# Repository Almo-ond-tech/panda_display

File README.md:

# panda_display

# Description

A spotify display in the form of a red pandas. You can see which song you're listening to, the album cover and the name of the artist on the display. Switch 1 goes to the previous song, switch 2 pauses the track and switch 3 skips the track you're currently listening to.
  
# Reason
I made this project as a gift for my friend who loves listening to music on spotify. I thought it would look nice as a decoration in their room and because they love red panda. The case is a bit too big, but I think it's fine since it also serves as an aesthetic features. They also like 3d modeling stuff so that's why I intentionally didn't model the keycaaps so they could customise it themselves.

# Firmware Setup
I used a spotify library that's a wrapper for the Spotify Web API designed to work with the ESP32 microcontroller from 
<a href= 'https://github.com/FinianLandes/SpotifyEsp32#setup'> FinianLandes/SpotifyEsp32. </a> It also contains a more in depth tutorial on how to set it up.
To start you should have a <b>spotify developer's account</b> and replace the <b>Client Id</b> and <b>Client Secret</b> with your own in the sketch. Then fill this in the redirect uri:

Enable the <b> Web API </b> option.

Also replace the ssid and password to match the wifi you're going to be using. If you don't know the ssid of your wifi network it will be printed in the serial monitor while the esp tries to connect to a nearby network. Then you can set the ssid and it will be connected to the internet.
After logging in via the URL shown in the Serial Monitor, your ESP32 will print a refresh token.
Copy this token and pass it as the third parameter to the constructor.
Spotify sp(CLIENT_ID, CLIENT_SECRET, REFRESH_TOKEN);

## Disclaimer
What I have now is currently untested so the firmware and the casing will definitely need some adjusting depending on how everything turns out

<h3><b>The blue crossed out pins on the display match the header pins in that exact order. Starting from pin 2 to pin 12</b></h3>

# Building the Case

<a href='https://cad.onshape.com/documents/bfc07541df551773d29ac83e/w/7fb00ae2864c3e517c62e19a/e/fd3725dd2f3859ce92e0f7f4'> Onshape Link </a> Or else copy paste in your browser : [https://cad.onshape.com/documents/bfc07541df551773d29ac83e/w/7fb00ae2864c3e517c62e19a/e/fd3725dd2f3859ce92e0f7f4]

<h4>Step 1:</h4> Glue all the componets for the Face and Tail indivudually after printing everything in your preferred colors with a strong adhesive. 
For the Body glue all the parts together <b>excluding the bottom case</b>.  <br>
 For the Face make sure to glue with the parts facing the right direction.  <br>
 For the Tail make sure to glue the parts in the right order.

<h4>Step 2:</h4> Attach the full case together <b>Still excluding the bottom case</b>.

<h4>Step 3:</h4> Fasten all the electrical pieces inside the Body. 

<h4>Step 4:</h4> 
Secure the bottom case in place and your Red Panda Display is now complete!

## BOM (Bill of Materials)
[tablemagic_with_total.csv](https://github.com/user-attachments/files/29109595/tablemagic_with_total.csv)

| Item                                                                                            | Description                               | Quantity | Unit Price ($) | Total Price | URL                                                                                                                                                                                                                                                                                                                                                                                                                                                                                                                                                                                                                                                                                                                                                                                                                                                                                                                                        | Running Total ($ with Tax) |
|-------------------------------------------------------------------------------------------------|-------------------------------------------|----------|----------------|-------------|--------------------------------------------------------------------------------------------------------------------------------------------------------------------------------------------------------------------------------------------------------------------------------------------------------------------------------------------------------------------------------------------------------------------------------------------------------------------------------------------------------------------------------------------------------------------------------------------------------------------------------------------------------------------------------------------------------------------------------------------------------------------------------------------------------------------------------------------------------------------------------------------------------------------------------------------|----------------------------|
| 1,8  ST7735S TFT LCD-scherm                                                                     | 128x160 ST7735S TFT LCD-screen            | 1        | 3.52           | 3.52        | https://nl.aliexpress.com/item/1005009694512284.html?spm=a2g0o.cart.0.0.53c261d7OkfEao&mp=1&pdp_npi=6%40dis%21EUR%21EUR+6.07%21EUR+3.04%21%21EUR+3.04%21%21%21%402161390417815650514934912e10d2%2112000049877275098%21ct%21NL%213328622363%21%211%210%21&gatewayAdapt=glo2nld                                                                                                                                                                                                                                                                                                                                                                                                                                                                                                                                                                                                                                                              | 3.52                       |
| 40pcs Dupont Wire Kabel 20 cm Female to Female                                                  | 20cm Dupont Wires (12pcs)                 | 1        | 0.0445         | 1.78        | https://nl.aliexpress.com/item/1005009071621102.html?spm=a2g0o.cart.0.0.53c261d7OkfEao&mp=1&pdp_npi=6%40dis%21EUR%21EUR+1.54%21EUR+1.54%21%21EUR+1.54%21%21%21%402161390417815650514934912e10d2%2112000047812726057%21ct%21NL%213328622363%21%211%210%21&gatewayAdapt=glo2nld                                                                                                                                                                                                                                                                                                                                                                                                                                                                                                                                                                                                                                                              | 1.78                       |
| 10 Pieces 2.54mm Single Row Pin Header Connector Strip 12Pin                                    | 12pin Pin Headers (1pc)                   | 1        | 0.207          | 2.07        | https://nl.aliexpress.com/item/4000988113226.html?spm=a2g0o.cart.0.0.53c261d7OkfEao&mp=1&pdp_npi=6%40dis%21EUR%21EUR+1.79%21EUR+1.79%21%21EUR+1.79%21%21%21%402161390417815650514934912e10d2%2110000013202368857%21ct%21NL%213328622363%21%211%210%21&gatewayAdapt=glo2nld                                                                                                                                                                                                                                                                                                                                                                                                                                                                                                                                                                                                                                                                 | 2.07                       |
| C3 PICO V1.0.0 - LOLIN WIFI Bluetooth IOT-bord ESP32-C3FH4                                      | MCU                                       | 1        | 7.77           | 7.77        | https://nl.aliexpress.com/item/1005004866531117.html?spm=a2g0o.cart.0.0.53c261d7OkfEao&mp=1&pdp_npi=6%40dis%21EUR%21EUR+6.69%21EUR+6.69%21%21EUR+6.69%21%21%21%402161390417815650514934912e10d2%2112000056168901173%21ct%21NL%213328622363%21%211%210%21&gatewayAdapt=glo2nld                                                                                                                                                                                                                                                                                                                                                                                                                                                                                                                                                                                                                                                              | 7.77                       |
| 20 Pieces Mechanical Keyboard Switches Red Hot-swappable 3-pin cross stem                       | Keyboard switches (3pcs)                  | 1        | 0.168          | 3.36        | https://nl.aliexpress.com/item/1005011838889689.html?spm=a2g0o.cart.0.0.53c261d7OkfEao&mp=1&pdp_npi=6%40dis%21EUR%21EUR+2.90%21EUR+2.90%21%21EUR+2.90%21%21%21%402161390417815650514934912e10d2%2112000056744509268%21ct%21NL%213328622363%21%211%210%21&gatewayAdapt=glo2nld                                                                                                                                                                                                                                                                                                                                                                                                                                                                                                                                                                                                                                                              | 3.36                       |
| Lithium Polymer Battery 3.7 V 500 mAh 403048 Lipo Rechargeable Battery with Wired JST Connector | Lipo Battery                              | 1        | 11.6           | 11.6        | https://www.amazon.nl/gp/product/B095W6742D/ref=ox_sc_act_title_1?smid=ASLRAS85RTYN3&th=1                                                                                                                                                                                                                                                                                                                                                                                                                                                                                                                                                                                                                                                                                                                                                                                                                                                  | 11.6                       |
| M2.5 screws (50 pcs)                                                                            | 2.5mm diameter pan head screws 6mm (2pcs) | 1        | 0.05           | 2.5         | https://nl.aliexpress.com/item/1005008709978631.html?spm=a2g0o.detail.pcDetailTopMoreOtherSeller.2.454fftMBftMBpy&gps-id=pcDetailTopMoreOtherSeller&scm=1007.40050.354490.0&scm_id=1007.40050.354490.0&scm-url=1007.40050.354490.0&pvid=83f03170-c03f-4f9e-a1b3-7860960ec42c&_t=gps-id%3ApcDetailTopMoreOtherSeller%2Cscm-url%3A1007.40050.354490.0%2Cpvid%3A83f03170-c03f-4f9e-a1b3-7860960ec42c%2Ctpp_buckets%3A668%232846%238114%231999&pdp_ext_f=%7B%22order%22%3A%2211679%22%2C%22eval%22%3A%221%22%2C%22sceneId%22%3A%2230050%22%2C%22fromPage%22%3A%22recommend%22%7D&pdp_npi=6%40dis%21EUR%211.96%211.80%21%21%2114.93%2113.73%21%400b884b5817817984658936804e0fbf%2112000046342342830%21rec%21NL%213328622363%21XZ%211%210%21n_tag%3A-29919%3Bd%3A9b918edc%3Bm03_new_user%3A-29895%3BpisId%3A5000000209393528&utparam-url=scene%3ApcDetailTopMoreOtherSeller%7Cquery_from%3A%7Cx_object_id%3A1005008709978631%7C_p_origin_prod%3A | 2.5                        |
| M3 screws (50 pcs)                                                                              | 3mm diameter pan head screws 6mm (4pcs)   | 1        | 0.0504         | 2.52        | https://nl.aliexpress.com/item/1005008709978631.html?spm=a2g0o.detail.pcDetailTopMoreOtherSeller.2.454fftMBftMBpy&gps-id=pcDetailTopMoreOtherSeller&scm=1007.40050.354490.0&scm_id=1007.40050.354490.0&scm-url=1007.40050.354490.0&pvid=83f03170-c03f-4f9e-a1b3-7860960ec42c&_t=gps-id%3ApcDetailTopMoreOtherSeller%2Cscm-url%3A1007.40050.354490.0%2Cpvid%3A83f03170-c03f-4f9e-a1b3-7860960ec42c%2Ctpp_buckets%3A668%232846%238114%231999&pdp_ext_f=%7B%22order%22%3A%2211679%22%2C%22eval%22%3A%221%22%2C%22sceneId%22%3A%2230050%22%2C%22fromPage%22%3A%22recommend%22%7D&pdp_npi=6%40dis%21EUR%211.96%211.80%21%21%2114.93%2113.73%21%400b884b5817817984658936804e0fbf%2112000046342342830%21rec%21NL%213328622363%21XZ%211%210%21n_tag%3A-29919%3Bd%3A9b918edc%3Bm03_new_user%3A-29895%3BpisId%3A5000000209393528&utparam-url=scene%3ApcDetailTopMoreOtherSeller%7Cquery_from%3A%7Cx_object_id%3A1005008709978631%7C_p_origin_prod%3A | 2.52                       |
| TOTAL                                                                                           |                                           |          |                | 35.12       |                                                                                                                                                                                                                                                                                                                                                                                                                                                                                                                                                                                                                                                                                                                                                                                                                                                                                                                                            |                            |

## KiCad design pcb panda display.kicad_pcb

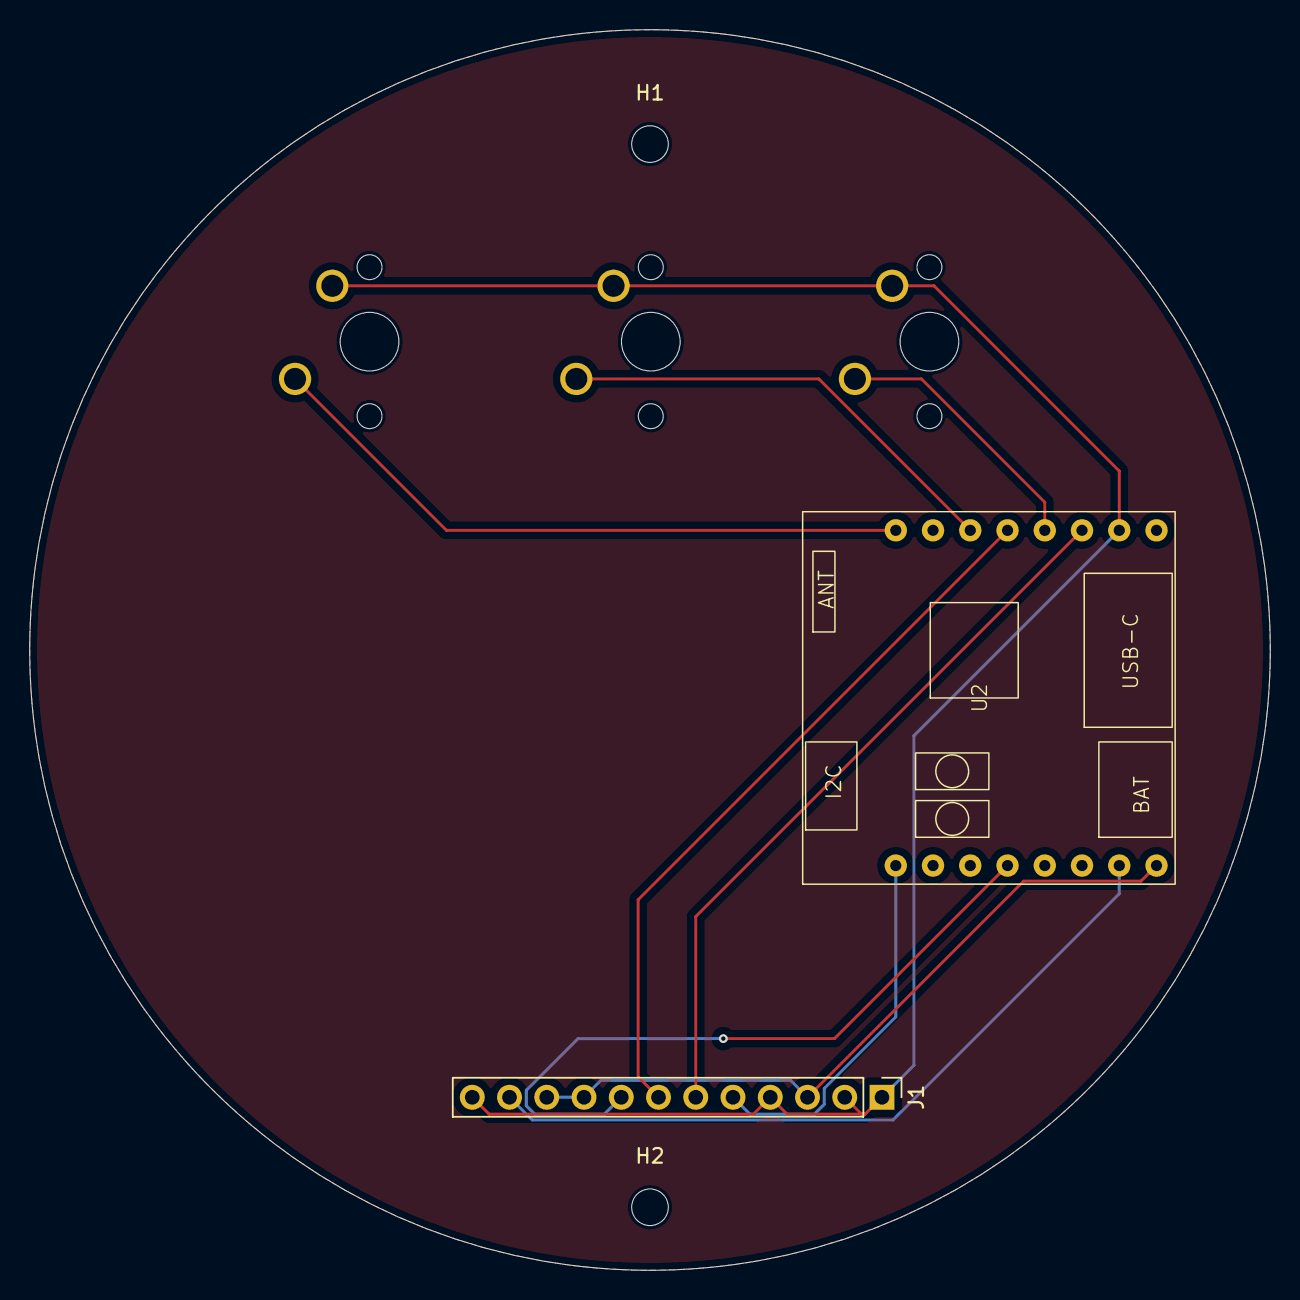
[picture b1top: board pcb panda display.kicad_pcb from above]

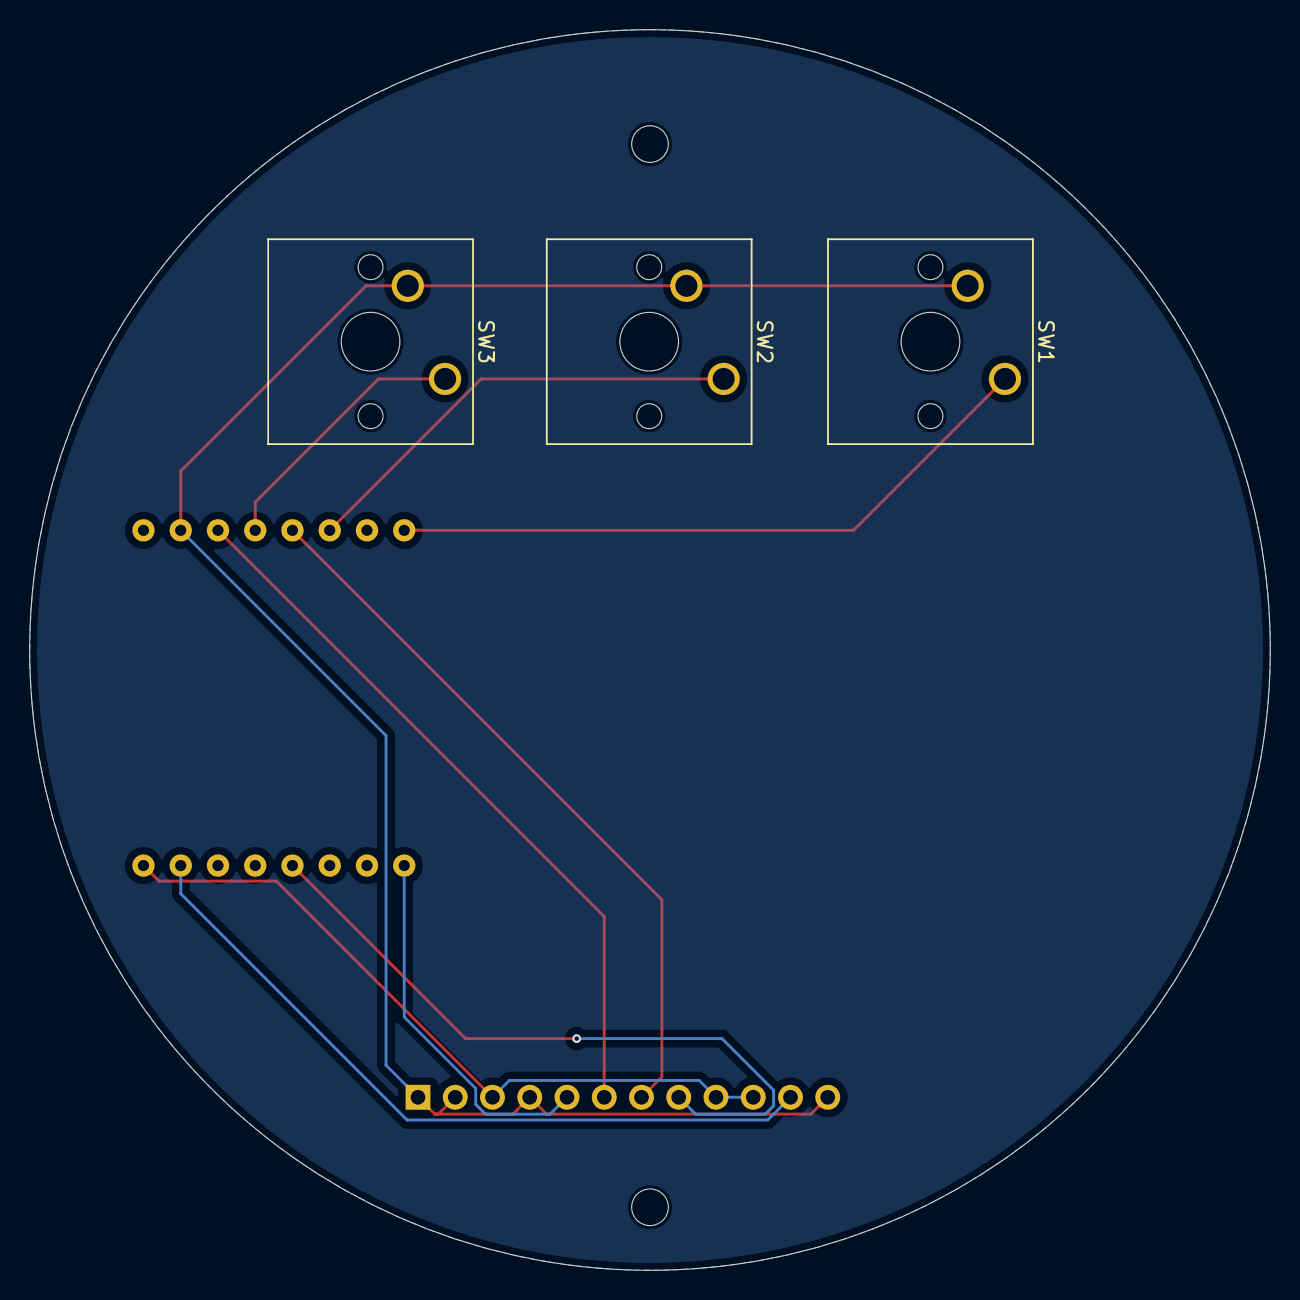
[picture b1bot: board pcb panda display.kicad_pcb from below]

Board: 2 copper layers, 84.6 x 84.6 mm, 7 parts (3 on the bottom side), 10 nets.

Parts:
H1, H2: MountingHole; MountingHole_2.5mm
J1: Conn_01x12_Pin; PinHeader_1x12_P2.54mm_Vertical
SW1, SW2, SW3: SW_Push; SW_Cherry_MX_1.00u_PCB
U2: C3 Pico; c3-pico

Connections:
+3.3V: J1.3, J1.9, J1.10, U2.9 (3V3)
GND: J1.1, J1.2, J1.4, J1.12, SW1.2, SW2.2, SW3.2, U2.2 (GND)
unnamed: J1.5, U2.16 (RST/EN)
unnamed: J1.6, U2.3 (IO6)
unnamed: J1.7, U2.5 (SDA/IO8)
unnamed: J1.8, U2.13 (IO1/ADC/SCK)
unnamed: J1.11, U2.10 (IO5)
unnamed: SW3.1, U2.4 (RGB/IO7)
unnamed: SW2.1, U2.6 (SCL/IO10)
unnamed: SW1.1, U2.8 (TX/IO21)

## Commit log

2026-06-07 Add TO DO section to README
    Added a TO DO section with project details and requirements.
2026-06-07 Add 3D images to README for better visualization
    Added images to enhance project documentation.
2026-06-15 Update README with additional project details and BOM
2026-06-18 Update README to streamline content
    Removed unnecessary contents section from README.
2026-06-18 Update README with project reason and usage details
    Added a reason for the project and usage instructions.
2026-06-18 Update README with Spotify library usage instructions
    Added usage instructions for the Spotify library and clarified setup steps.
2026-06-18 Update comments for button actions in sketch
2026-06-18 Add image to README for panda display project
2026-06-18 Fix duplicate entry for M3 screws in README
2026-06-18 Update BOM with additional items and links
2026-06-18 Fix grammatical error in project description
    Corrected the description to use 'red pandas' instead of 'red panda'.
2026-06-18 Add BOM section with item details and total cost
    Added a Bill of Materials section with item details and total cost.
2026-06-18 Add assembly instructions for panda case
    Added instructions for attaching components to the panda case.
2026-06-18 Enhance README with assembly images and link
    Added images and an Onshape link for assembly instructions.
2026-06-18 Fix Onshape link formatting in README
    Updated the Onshape link to use Markdown formatting.
2026-06-18 Fix Onshape link and improve README formatting
    Updated the Onshape link for clarity and corrected formatting.
2026-06-18 Add Onshape link to README
2026-06-18 Fix Onshape link formatting in README
    Updated Onshape link formatting and added instructions for copying the link.
2026-06-18 Clarify usage of Spotify library in README
    Updated the description of the Spotify library usage.
2026-06-18 Rename schematics.png to docs/schematics.png
2026-06-18 Rename BOM.csv to docs/BOM.csv
2026-06-18 Rename panda display pcb.png to docs/panda display pcb.png
2026-06-18 Rename panda display pcb.png to panda_display_pcb.png
2026-06-18 Rename pcb panda display.kicad_pcb to hardware/pcb_panda_display.kicad_pcb
2026-06-18 Rename pcb panda display.kicad_pro to hardware/pcb_panda_display.kicad_pro
2026-06-18 Rename pcb panda display.kicad_sch to hardware/pcb_panda_display.kicad_sch
2026-06-18 Rename pcb panda display.step to pcb_panda_display.step
2026-06-18 Rename pcb_panda_display.step to hardware/pcb_panda_display.step
2026-06-18 Revise README with Spotify setup instructions
    Updated usage instructions for Spotify integration and added details about obtaining a refresh token.
2026-06-18 Fix wording in README for WiFi setup instructions
2026-06-18 Revise README with updated Spotify setup instructions
    Updated usage instructions for Spotify library and added details on setting up the ESP32.
2026-06-18 Update README formatting and content
2026-06-21 Create what?
2026-06-21 Create random
2026-06-21 Rename random to body
2026-06-21 Create tail
2026-06-21 Rename body to main body
2026-06-21 Create face
2026-06-21 Revise attachment instructions and fix typos
    Updated instructions for attaching components and fixed typos in the Onshape link.
2026-06-21 Revise README for firmware setup and case building
    Updated the README to improve clarity on setup and assembly instructions.
